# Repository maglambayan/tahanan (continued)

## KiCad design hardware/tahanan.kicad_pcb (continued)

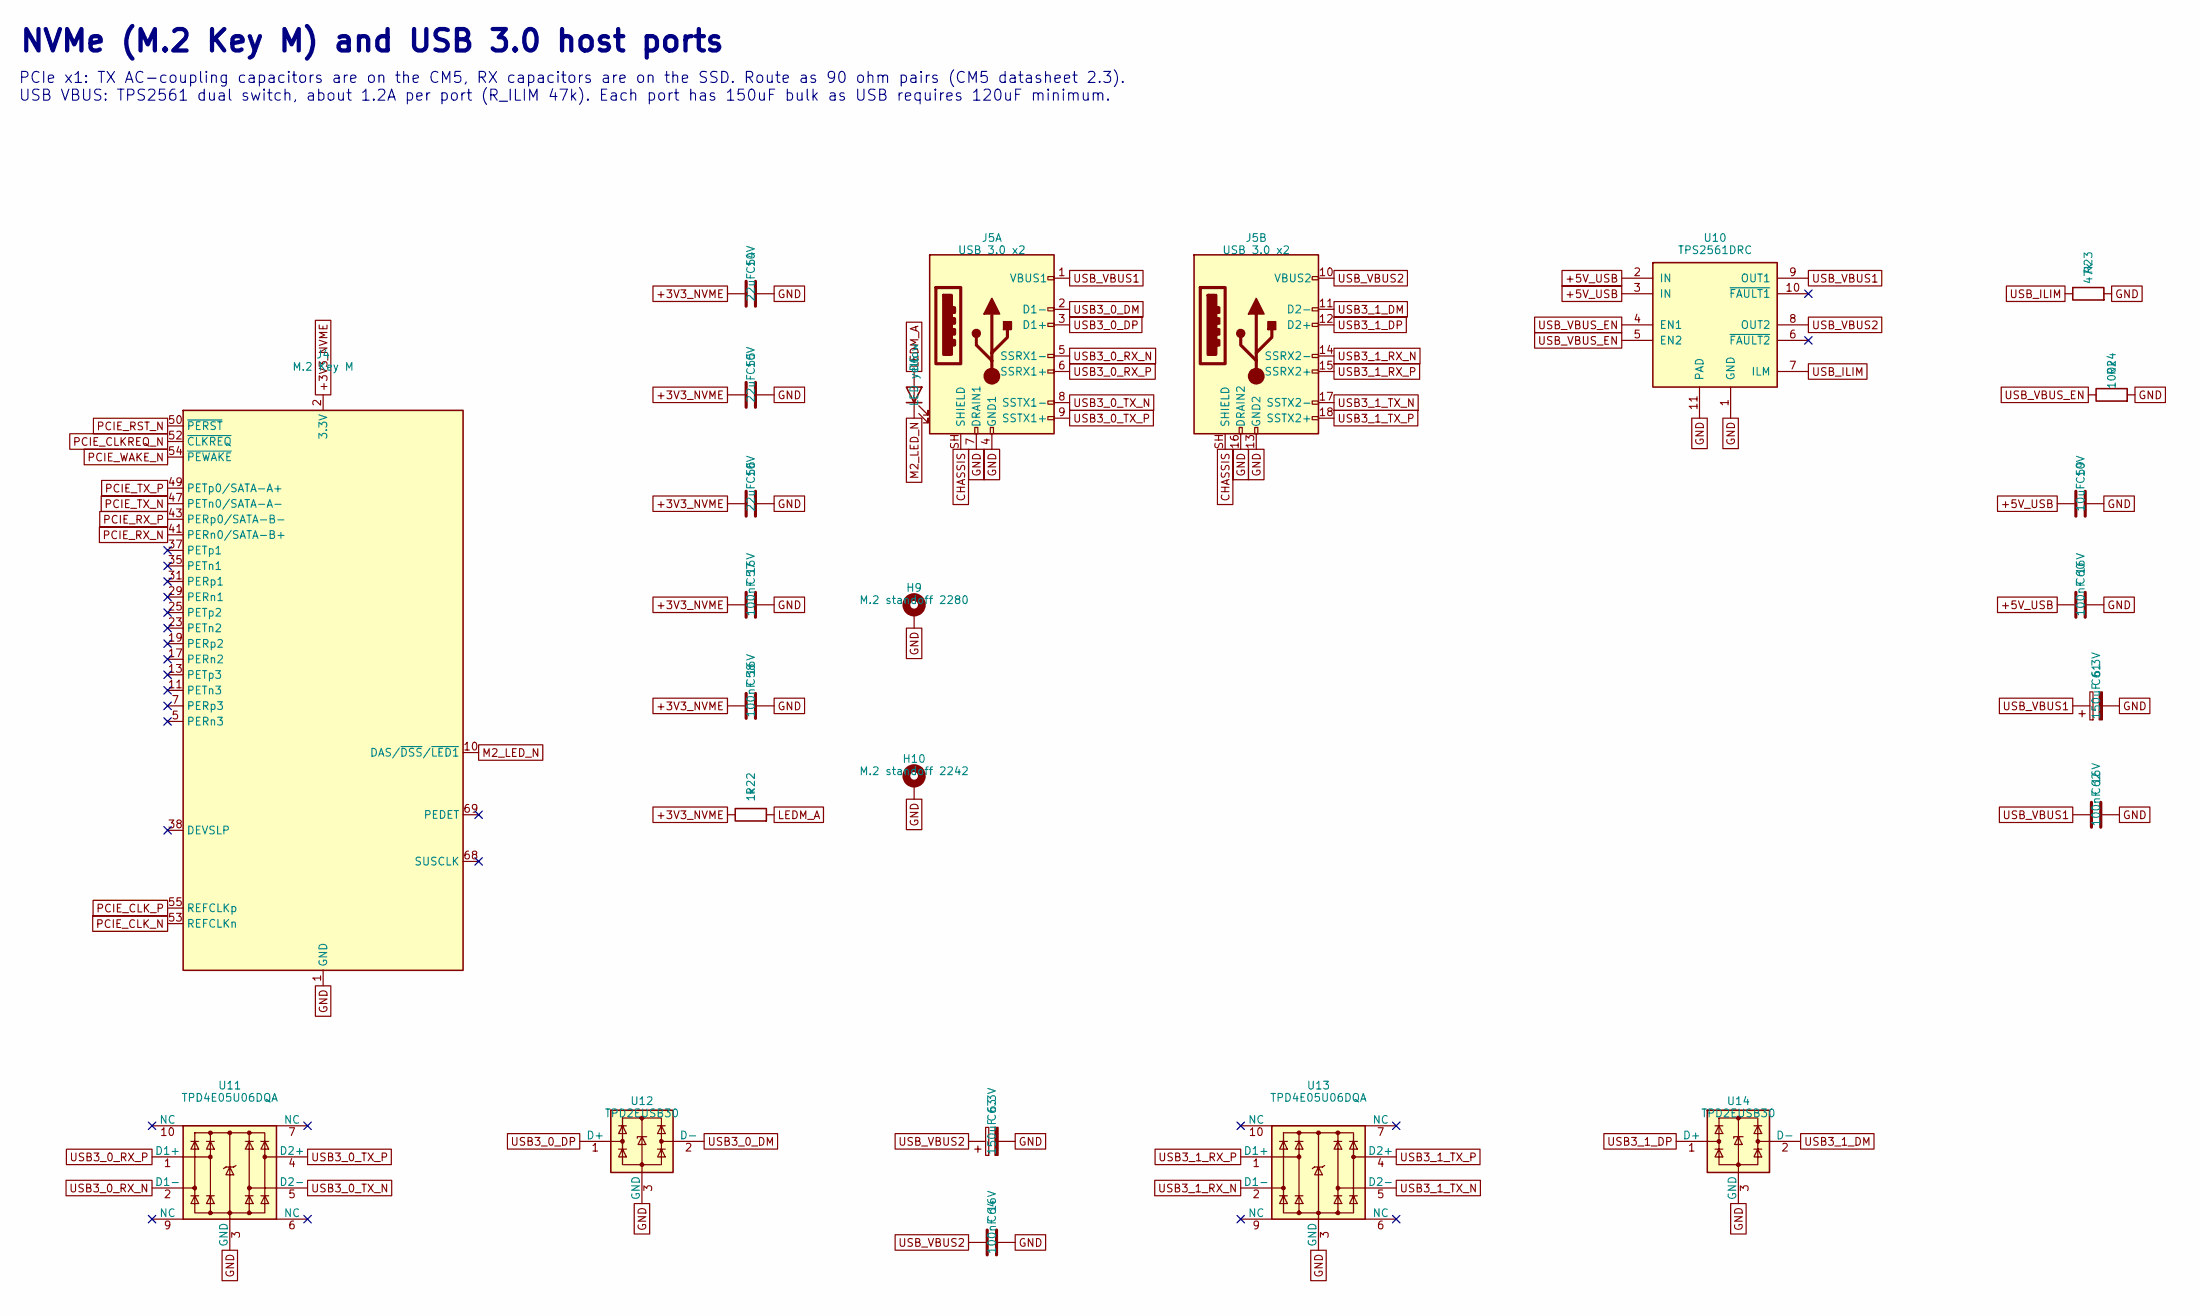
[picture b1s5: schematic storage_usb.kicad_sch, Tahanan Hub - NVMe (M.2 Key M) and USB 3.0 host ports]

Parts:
C54, C55, C56: 22uF 10V; C_0805_2012Metric; MPN CL21A226MPQNNNE
C57, C58, C60, C62, C64: 100nF 16V; C_0402_1005Metric; MPN CL05B104KO5NNNC
C59: 10uF 10V; C_0603_1608Metric; MPN CL10A106KP8NNNC
C61, C63: 150uF 6.3V; CP_EIA-3528-21_Kemet-B; MPN T520B157M006ATE070
D6: LED yellow; LED_0603_1608Metric; MPN 150060YS75000
H9: M.2 standoff 2280; Mounting_Wuerth_WA-SMSI-M2_H2.5mm_9774025243; MPN 9774025243R
H10: M.2 standoff 2242; Mounting_Wuerth_WA-SMSI-M2_H2.5mm_9774025243; MPN 9774025243R
J4: M.2 Key M; TE_M.2_M_2x38-1MP_P0.5mm; MPN 2199119-4
J5: USB 3.0 x2; USB3_A_Molex_48406-0001_Horizontal_Stacked; MPN 48406-0001
R22: 1k; R_0402_1005Metric; MPN RC0402FR-071kL
R23: 47k; R_0402_1005Metric; MPN RC0402FR-0747kL
R24: 100k; R_0402_1005Metric; MPN RC0402FR-07100kL
U10: TPS2561DRC; VSON-10-1EP_3x3mm_P0.5mm_EP1.65x2.4mm_ThermalVias; MPN TPS2561DRCR
U11, U13: TPD4E05U06DQA; USON-10_2.5x1.0mm_P0.5mm; MPN TPD4E05U06DQAR
U12, U14: TPD2EUSB30; Texas_DRT-3; MPN TPD2EUSB30DRTR

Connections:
+3V3_NVME: C54.1, C55.1, C56.1, C57.1, C58.1, J4.2 (3.3V), J4.4 (3.3V), J4.12 (3.3V), J4.14 (3.3V), J4.16 (3.3V), J4.18 (3.3V), J4.70 (3.3V), J4.72 (3.3V), J4.74 (3.3V), R22.1; also elsewhere on the board
+5V_USB: C59.1, C60.1, U10.2 (IN), U10.3 (IN); also elsewhere on the board
CHASSIS: J5.SH (SHIELD); also elsewhere on the board
GND: C54.2, C55.2, C56.2, C57.2, C58.2, C59.2, C60.2, C61.2, C62.2, C63.2, C64.2, H9.1, H10.1, J4.1 (GND), J4.3 (GND), J4.9 (GND), J4.15 (GND), J4.21 (GND), J4.27 (GND), J4.33 (GND), J4.39 (GND), J4.45 (GND), J4.51 (GND), J4.57 (GND), J4.71 (GND), J4.73 (GND), J4.75 (GND), J5.4 (GND1), J5.7 (DRAIN1), J5.13 (GND2), J5.16 (DRAIN2), R23.2, R24.2, U10.1 (GND), U10.11 (PAD), U11.3 (GND), U11.8 (GND), U12.3 (GND), U13.3 (GND), U13.8 (GND), U14.3 (GND); also elsewhere on the board
LEDM_A: D6.2 (A), R22.2
M2_LED_N: D6.1 (K), J4.10 (DAS/~DSS/~LED1)
PCIE_CLKREQ_N: J4.52 (~CLKREQ); also elsewhere on the board
PCIE_CLK_N: J4.53 (REFCLKn); also elsewhere on the board
PCIE_CLK_P: J4.55 (REFCLKp); also elsewhere on the board
PCIE_RST_N: J4.50 (~PERST); also elsewhere on the board
PCIE_RX_N: J4.41 (PERn0/SATA-B+); also elsewhere on the board
PCIE_RX_P: J4.43 (PERp0/SATA-B-); also elsewhere on the board
PCIE_TX_N: J4.47 (PETn0/SATA-A-); also elsewhere on the board
PCIE_TX_P: J4.49 (PETp0/SATA-A+); also elsewhere on the board
PCIE_WAKE_N: J4.54 (~PEWAKE); also elsewhere on the board
USB3_0_DM: J5.2 (D1-), U12.2 (D-); also elsewhere on the board
USB3_0_DP: J5.3 (D1+), U12.1 (D+); also elsewhere on the board
USB3_0_RX_N: J5.5 (SSRX1-), U11.2 (D1-); also elsewhere on the board
USB3_0_RX_P: J5.6 (SSRX1+), U11.1 (D1+); also elsewhere on the board
USB3_0_TX_N: J5.8 (SSTX1-), U11.5 (D2-); also elsewhere on the board
USB3_0_TX_P: J5.9 (SSTX1+), U11.4 (D2+); also elsewhere on the board
USB3_1_DM: J5.11 (D2-), U14.2 (D-); also elsewhere on the board
USB3_1_DP: J5.12 (D2+), U14.1 (D+); also elsewhere on the board
USB3_1_RX_N: J5.14 (SSRX2-), U13.2 (D1-); also elsewhere on the board
USB3_1_RX_P: J5.15 (SSRX2+), U13.1 (D1+); also elsewhere on the board
USB3_1_TX_N: J5.17 (SSTX2-), U13.5 (D2-); also elsewhere on the board
USB3_1_TX_P: J5.18 (SSTX2+), U13.4 (D2+); also elsewhere on the board
USB_ILIM: R23.1, U10.7 (ILM)
USB_VBUS1: C61.1, C62.1, J5.1 (VBUS1), U10.9 (OUT1)
USB_VBUS2: C63.1, C64.1, J5.10 (VBUS2), U10.8 (OUT2)
USB_VBUS_EN: R24.1, U10.4 (EN1), U10.5 (EN2); also elsewhere on the board

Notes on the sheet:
NVMe (M.2 Key M) and USB 3.0 host ports
PCIe x1: TX AC-coupling capacitors are on the CM5, RX capacitors are on the SSD. Route as 90 ohm pairs (CM5 datasheet 2.3). USB VBUS: TPS2561 dual switch, about 1.2A per port (R_ILIM 47k). Each port has 150uF bulk as USB requires 120uF minimum.

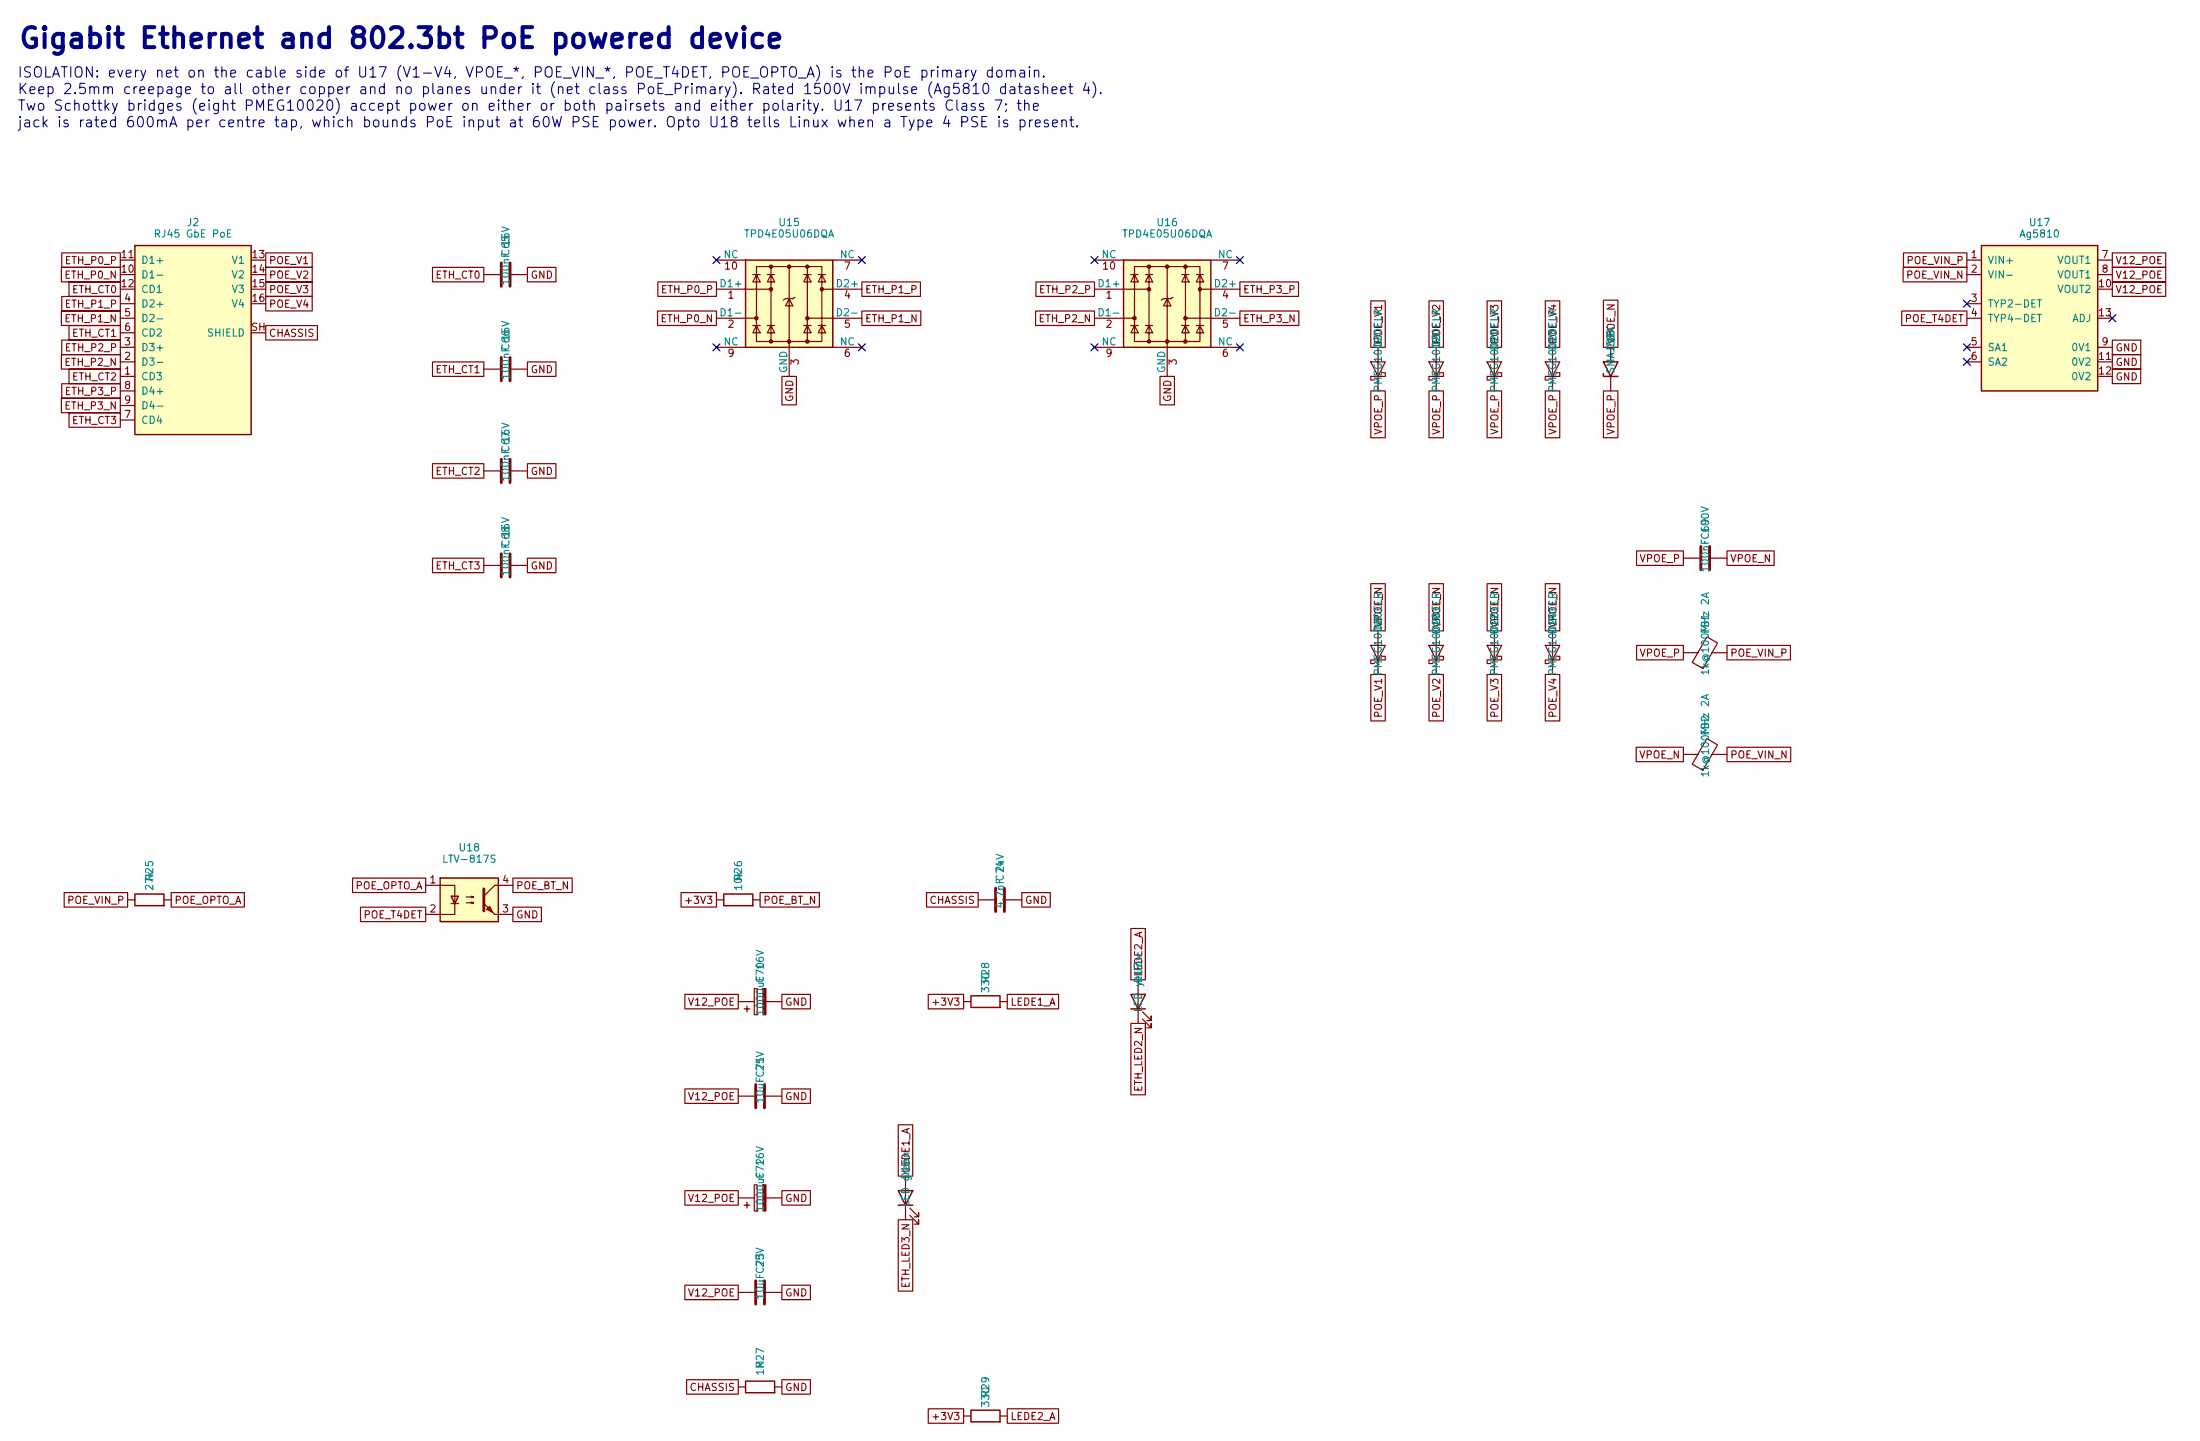
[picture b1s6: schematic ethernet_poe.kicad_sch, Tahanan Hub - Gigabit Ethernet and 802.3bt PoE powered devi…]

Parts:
C65, C66, C67, C68: 100nF 16V; C_0402_1005Metric; MPN CL05B104KO5NNNC
C69: 100nF 100V; C_0805_2012Metric; MPN CL21B104KCFNNNE
C70, C72: 1000uF 16V; CP_Elec_10x10.5; MPN EEE-FT1C102AP
C71, C73: 10uF 25V; C_1206_3216Metric; MPN CL31B106KAHNNNE
C74: 4.7nF 2kV; C_1812_4532Metric; MPN C1812C472KGRACTU
D7, D8, D9, D10, D11, D12, D13, D14: PMEG10020ELR; Nexperia_CFP3_SOD-123W; MPN PMEG10020ELRX
D15: SMAJ58A; D_SMA; MPN SMAJ58A
D16: LED green; LED_0603_1608Metric; MPN 150060GS75000
D17: LED yellow; LED_0603_1608Metric; MPN 150060YS75000
FB1, FB2: 1k@100MHz 2A; L_1210_3225Metric; MPN FBMH3225HM102NT
J2: RJ45 GbE PoE; RJ45_Wuerth_7499511001A; MPN 7499511001A
R25: 27k; R_1206_3216Metric; MPN RC1206FR-0727kL
R26: 10k; R_0402_1005Metric; MPN RC0402FR-0710kL
R27: 1M; R_1206_3216Metric; MPN RC1206FR-071ML
R28, R29: 330; R_0402_1005Metric; MPN RC0402FR-07330RL
U15, U16: TPD4E05U06DQA; USON-10_2.5x1.0mm_P0.5mm; MPN TPD4E05U06DQAR
U17: Ag5810; Silvertel_Ag5810; MPN Ag5810
U18: LTV-817S; SMDIP-4_W9.53mm; MPN LTV-817S

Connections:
+3V3: R26.1, R28.1, R29.1; also elsewhere on the board
CHASSIS: C74.1, J2.SH (SHIELD), R27.1; also elsewhere on the board
ETH_CT0: C65.1, J2.12 (CD1)
ETH_CT1: C66.1, J2.6 (CD2)
ETH_CT2: C67.1, J2.1 (CD3)
ETH_CT3: C68.1, J2.7 (CD4)
ETH_LED2_N: D17.1 (K); also elsewhere on the board
ETH_LED3_N: D16.1 (K); also elsewhere on the board
ETH_P0_N: J2.10 (D1-), U15.2 (D1-); also elsewhere on the board
ETH_P0_P: J2.11 (D1+), U15.1 (D1+); also elsewhere on the board
ETH_P1_N: J2.5 (D2-), U15.5 (D2-); also elsewhere on the board
ETH_P1_P: J2.4 (D2+), U15.4 (D2+); also elsewhere on the board
ETH_P2_N: J2.2 (D3-), U16.2 (D1-); also elsewhere on the board
ETH_P2_P: J2.3 (D3+), U16.1 (D1+); also elsewhere on the board
ETH_P3_N: J2.9 (D4-), U16.5 (D2-); also elsewhere on the board
ETH_P3_P: J2.8 (D4+), U16.4 (D2+); also elsewhere on the board
GND: C65.2, C66.2, C67.2, C68.2, C70.2, C71.2, C72.2, C73.2, C74.2, R27.2, U15.3 (GND), U15.8 (GND), U16.3 (GND), U16.8 (GND), U17.9 (0V1), U17.11 (0V2), U17.12 (0V2), U18.3; also elsewhere on the board
LEDE1_A: D16.2 (A), R28.2
LEDE2_A: D17.2 (A), R29.2
POE_BT_N: R26.2, U18.4; also elsewhere on the board
POE_OPTO_A: R25.2, U18.1
POE_T4DET: U17.4 (TYP4-DET), U18.2
POE_V1: D7.2 (A), D8.1 (K), J2.13 (V1)
POE_V2: D9.2 (A), D10.1 (K), J2.14 (V2)
POE_V3: D11.2 (A), D12.1 (K), J2.15 (V3)
POE_V4: D13.2 (A), D14.1 (K), J2.16 (V4)
POE_VIN_N: FB2.2, U17.2 (VIN-)
POE_VIN_P: FB1.2, R25.1, U17.1 (VIN+)
V12_POE: C70.1, C71.1, C72.1, C73.1, U17.7 (VOUT1), U17.8 (VOUT1), U17.10 (VOUT2); also elsewhere on the board
VPOE_N: C69.2, D8.2 (A), D10.2 (A), D12.2 (A), D14.2 (A), D15.2 (A2), FB2.1
VPOE_P: C69.1, D7.1 (K), D9.1 (K), D11.1 (K), D13.1 (K), D15.1 (A1), FB1.1

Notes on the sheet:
Gigabit Ethernet and 802.3bt PoE powered device
ISOLATION: every net on the cable side of U17 (V1-V4, VPOE_*, POE_VIN_*, POE_T4DET, POE_OPTO_A) is the PoE primary domain. Keep 2.5mm creepage to all other copper and no planes under it (net class PoE_Primary). Rated 1500V impulse (Ag5810 datasheet 4). Two Schottky bridges (eight PMEG10020) accept 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

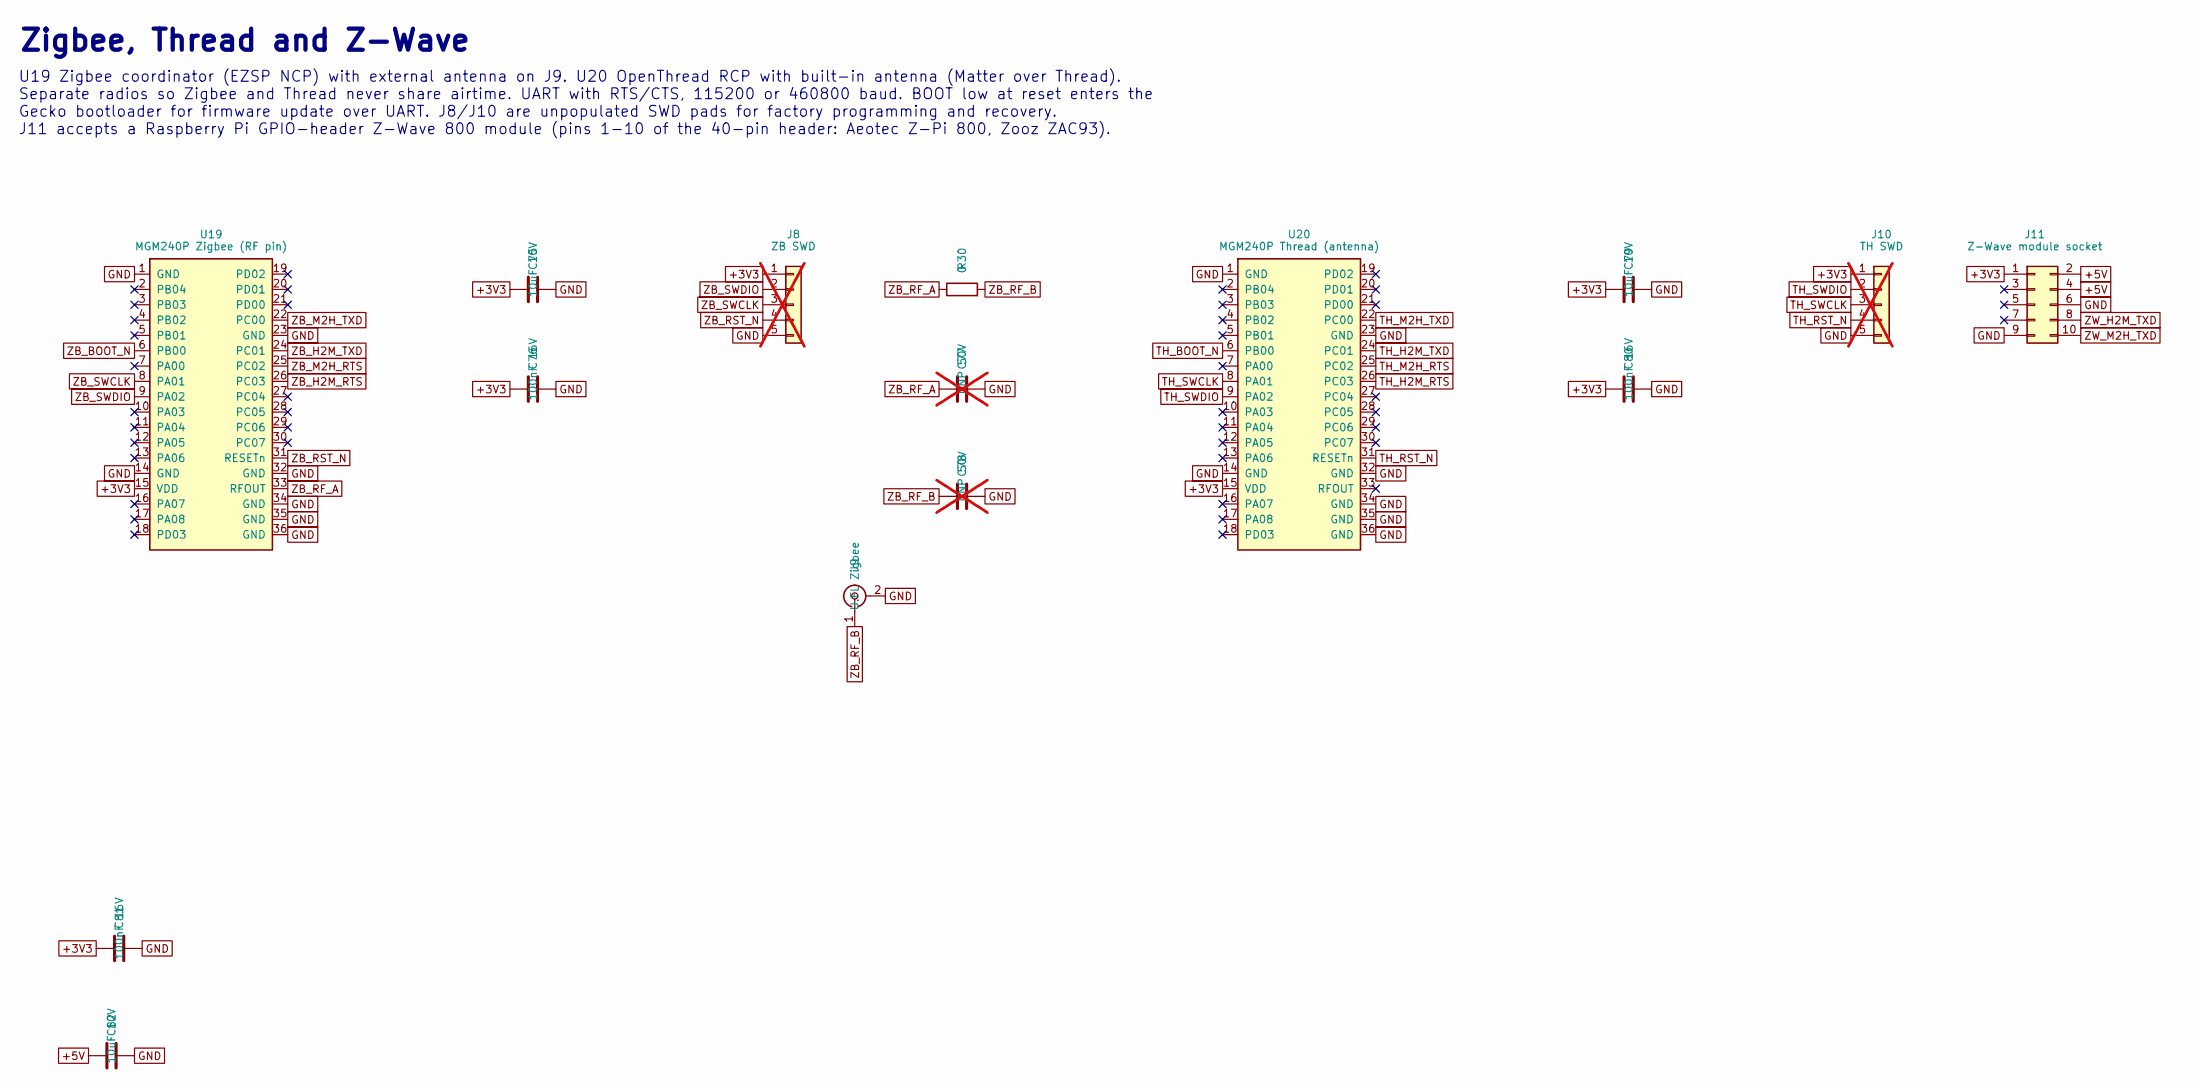
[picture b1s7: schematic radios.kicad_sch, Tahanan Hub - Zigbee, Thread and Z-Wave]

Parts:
C75, C79, C82: 10uF 10V; C_0603_1608Metric; MPN CL10A106KP8NNNC
C76, C80, C81: 100nF 16V; C_0402_1005Metric; MPN CL05B104KO5NNNC
C77, C78: DNP 50V; C_0402_1005Metric; not fitted
J8: ZB SWD; PinHeader_1x05_P1.27mm_Vertical; not fitted
J9: U.FL Zigbee; U.FL_Hirose_U.FL-R-SMT-1_Vertical; MPN U.FL-R-SMT-1(80)
J10: TH SWD; PinHeader_1x05_P1.27mm_Vertical; not fitted
J11: Z-Wave module socket; PinSocket_2x05_P2.54mm_Vertical; MPN SSW-105-01-G-D
R30: 0; R_0402_1005Metric; MPN RC0402FR-070RL
U19: MGM240P Zigbee (RF pin); SiliconLabs_MGM240P; MPN MGM240PA32VNN3
U20: MGM240P Thread (antenna); SiliconLabs_MGM240P; MPN MGM240PA32VNA3

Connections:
+3V3: C75.1, C76.1, C79.1, C80.1, C81.1, J8.1, J10.1, J11.1, U19.15 (VDD), U20.15 (VDD); also elsewhere on the board
+5V: C82.1, J11.2, J11.4; also elsewhere on the board
GND: C75.2, C76.2, C77.2, C78.2, C79.2, C80.2, C81.2, C82.2, J8.5, J9.2 (Ext), J10.5, J11.6, J11.9, U19.1 (GND), U19.14 (GND), U19.23 (GND), U19.32 (GND), U19.34 (GND), U19.35 (GND), U19.36 (GND), U20.1 (GND), U20.14 (GND), U20.23 (GND), U20.32 (GND), U20.34 (GND), U20.35 (GND), U20.36 (GND); also elsewhere on the board
TH_BOOT_N: U20.6 (PB00); also elsewhere on the board
TH_H2M_RTS: U20.26 (PC03); also elsewhere on the board
TH_H2M_TXD: U20.24 (PC01); also elsewhere on the board
TH_M2H_RTS: U20.25 (PC02); also elsewhere on the board
TH_M2H_TXD: U20.22 (PC00); also elsewhere on the board
TH_RST_N: J10.4, U20.31 (RESETn); also elsewhere on the board
TH_SWCLK: J10.3, U20.8 (PA01)
TH_SWDIO: J10.2, U20.9 (PA02)
ZB_BOOT_N: U19.6 (PB00); also elsewhere on the board
ZB_H2M_RTS: U19.26 (PC03); also elsewhere on the board
ZB_H2M_TXD: U19.24 (PC01); also elsewhere on the board
ZB_M2H_RTS: U19.25 (PC02); also elsewhere on the board
ZB_M2H_TXD: U19.22 (PC00); also elsewhere on the board
ZB_RF_A: C77.1, R30.1, U19.33 (RFOUT)
ZB_RF_B: C78.1, J9.1 (In), R30.2
ZB_RST_N: J8.4, U19.31 (RESETn); also elsewhere on the board
ZB_SWCLK: J8.3, U19.8 (PA01)
ZB_SWDIO: J8.2, U19.9 (PA02)
ZW_H2M_TXD: J11.8; also elsewhere on the board
ZW_M2H_TXD: J11.10; also elsewhere on the board

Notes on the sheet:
Zigbee, Thread and Z-Wave
U19 Zigbee coordinator (EZSP NCP) with external antenna on J9. U20 OpenThread RCP with built-in antenna (Matter over Thread). Separate radios so Zigbee and Thread never share airtime. UART with RTS/CTS, 115200 or 460800 baud. BOOT low at reset enters the Gecko bootloader for firmware update over UA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

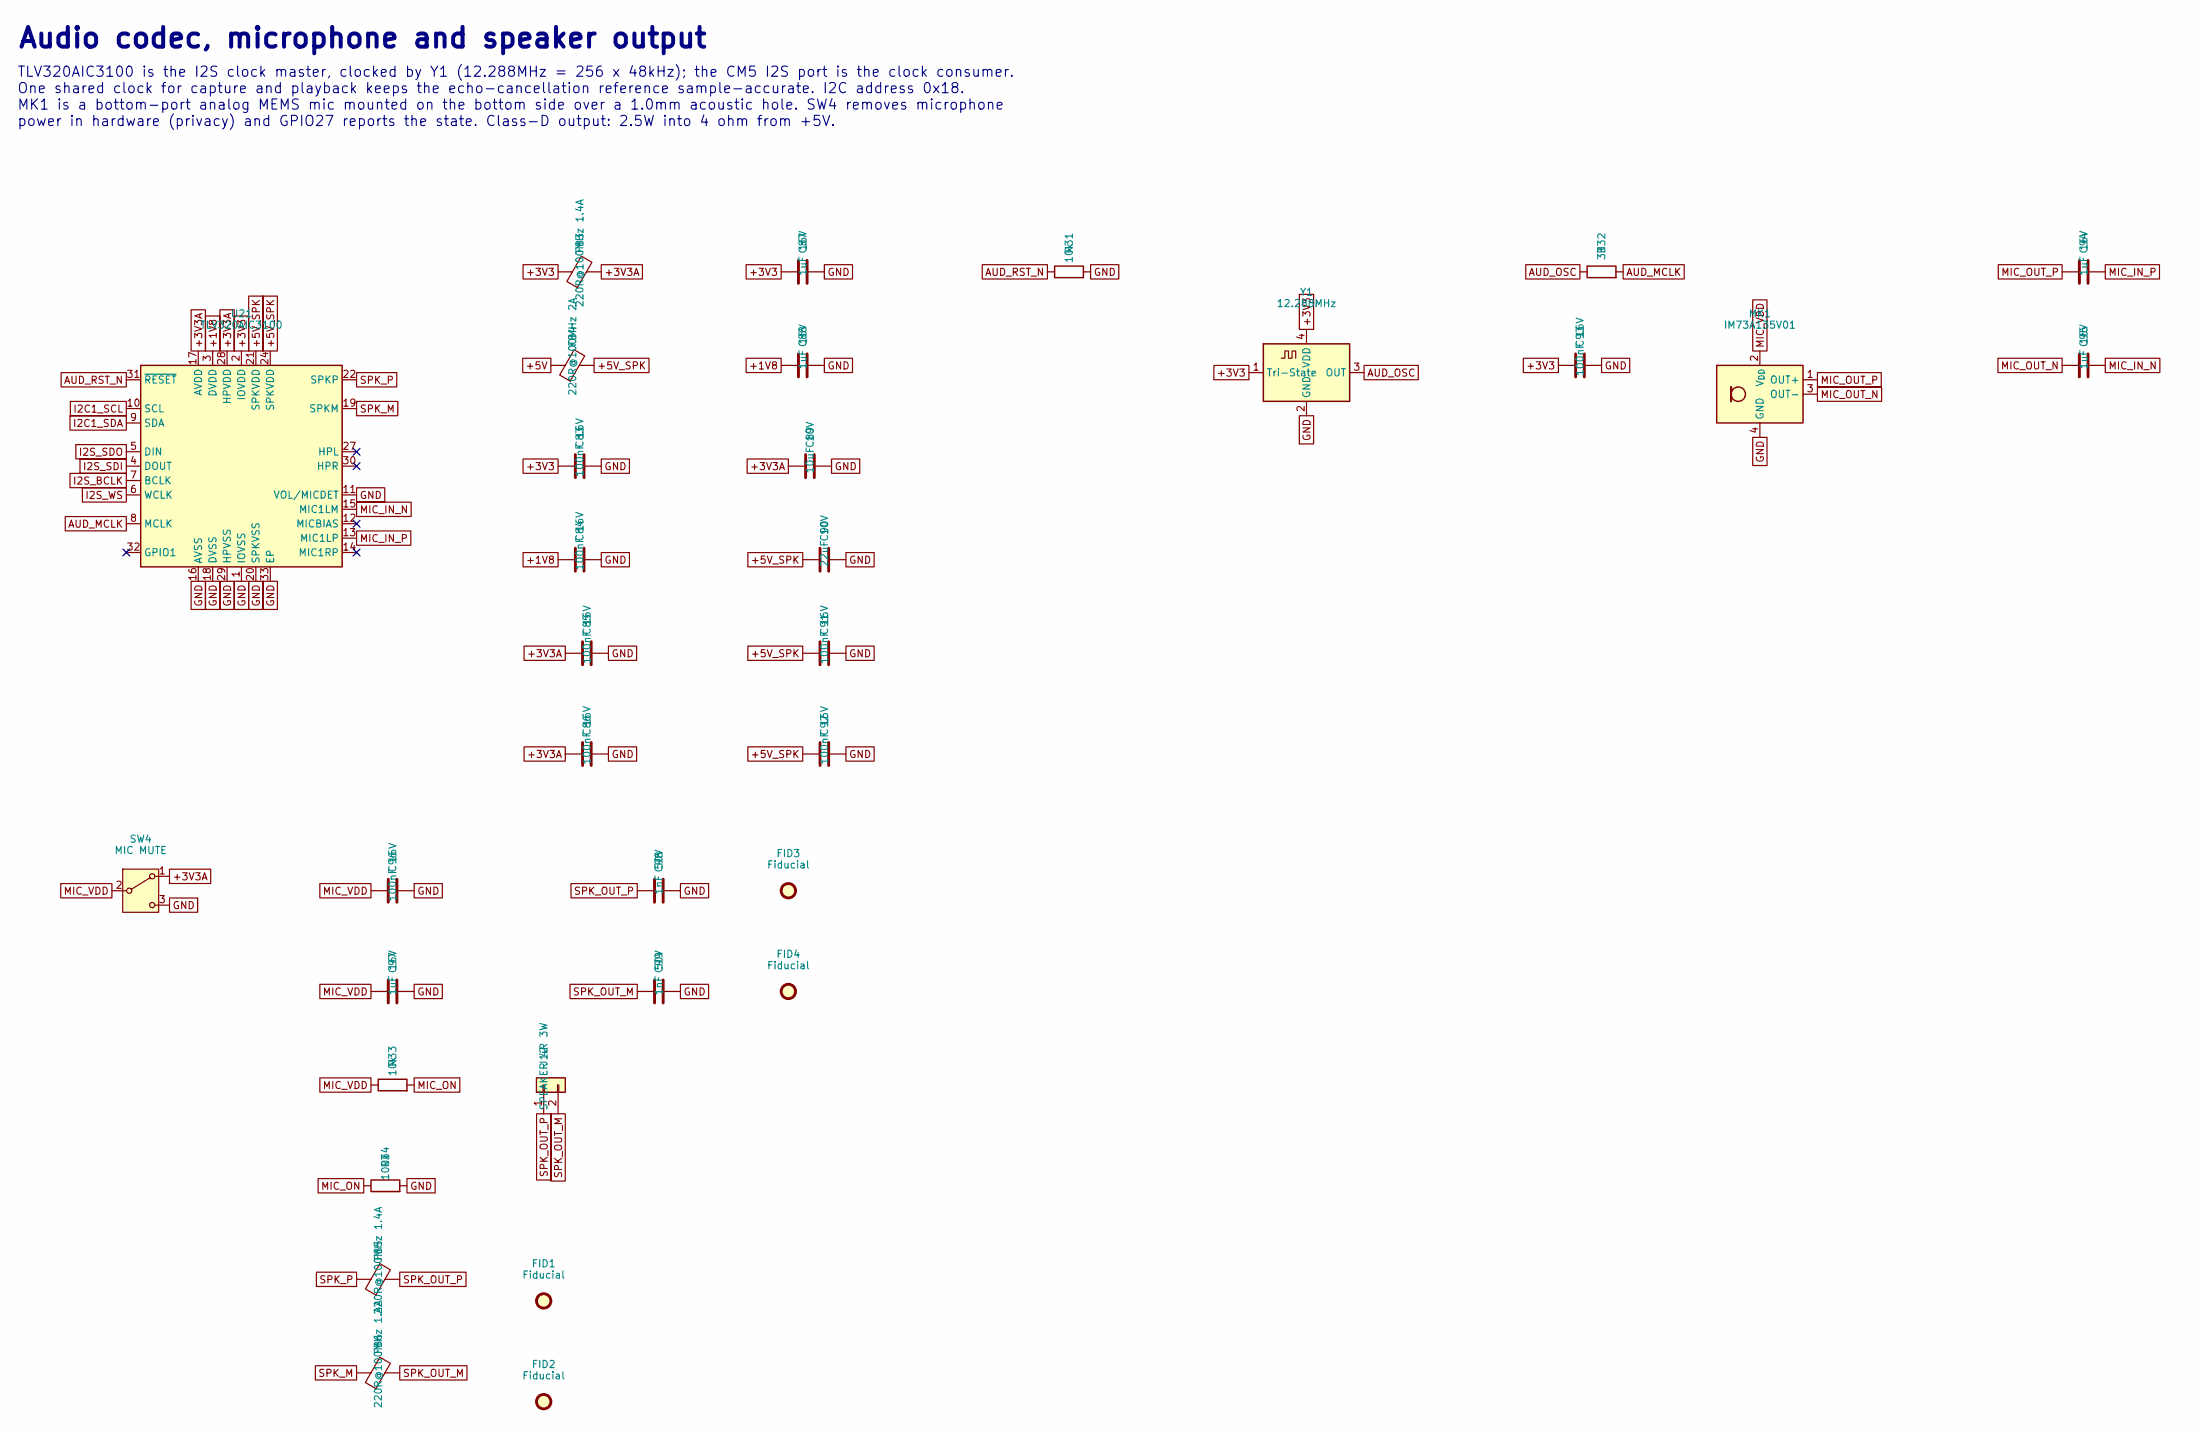
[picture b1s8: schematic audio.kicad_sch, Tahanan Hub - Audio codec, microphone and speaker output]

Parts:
C83, C84, C85, C86, C91, C92, C93, C96: 100nF 16V; C_0402_1005Metric; MPN CL05B104KO5NNNC
C87, C88, C94, C95, C97: 1uF 16V; C_0402_1005Metric; MPN CL05A105KO5NNNC
C89: 10uF 10V; C_0603_1608Metric; MPN CL10A106KP8NNNC
C90: 22uF 10V; C_0805_2012Metric; MPN CL21A226MPQNNNE
C98, C99: 1nF 50V; C_0402_1005Metric; MPN CL05B102KB5NNNC
FB3, FB5, FB6: 220R@100MHz 1.4A; L_0603_1608Metric; MPN BLM18PG221SN1D
FB4: 220R@100MHz 2A; L_0805_2012Metric; MPN BLM21PG221SN1D
FID1, FID2, FID3, FID4: Fiducial; Fiducial_1mm_Mask2mm
J12: SPEAKER 4R 3W; JST_PH_S2B-PH-K_1x02_P2.00mm_Horizontal; MPN S2B-PH-K-S
MK1: IM73A135V01; Infineon_PG-LLGA-5-2; MPN IM73A135V01XTSA1
R31, R33: 10k; R_0402_1005Metric; MPN RC0402FR-0710kL
R32: 33; R_0402_1005Metric; MPN RC0402FR-0733RL
R34: 100k; R_0402_1005Metric; MPN RC0402FR-07100kL
SW4: MIC MUTE; SW_SPDT_CK_JS102011SAQN; MPN JS102011SAQN
U21: TLV320AIC3100; VQFN-32-1EP_5x5mm_P0.5mm_EP3.5x3.5mm; MPN TLV320AIC3100IRHBR
Y1: 12.288MHz; Oscillator_SMD_ECS_2520MV-xxx-xx-4Pin_2.5x2.0mm; MPN ECS-2520MVLC-122.8-BN-TR

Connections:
+1V8: C84.1, C88.1, U21.3 (DVDD); also elsewhere on the board
+3V3: C83.1, C87.1, C93.1, FB3.1, U21.2 (IOVDD), Y1.1 (Tri-State), Y1.4 (VDD); also elsewhere on the board
+3V3A: C85.1, C86.1, C89.1, FB3.2, SW4.1 (A), U21.17 (AVDD), U21.28 (HPVDD)
+5V: FB4.1; also elsewhere on the board
+5V_SPK: C90.1, C91.1, C92.1, FB4.2, U21.21 (SPKVDD), U21.24 (SPKVDD)
AUD_MCLK: R32.2, U21.8 (MCLK)
AUD_OSC: R32.1, Y1.3 (OUT)
AUD_RST_N: R31.1, U21.31 (~RESET); also elsewhere on the board
GND: C83.2, C84.2, C85.2, C86.2, C87.2, C88.2, C89.2, C90.2, C91.2, C92.2, C93.2, C96.2, C97.2, C98.2, C99.2, MK1.4 (GND), MK1.5 (GND), R31.2, R34.2, SW4.3 (C), U21.1 (IOVSS), U21.11 (VOL/MICDET), U21.16 (AVSS), U21.18 (DVSS), U21.20 (SPKVSS), U21.25 (SPKVSS), U21.29 (HPVSS), U21.33 (EP), Y1.2 (GND); also elsewhere on the board
I2C1_SCL: U21.10 (SCL); also elsewhere on the board
I2C1_SDA: U21.9 (SDA); also elsewhere on the board
I2S_BCLK: U21.7 (BCLK); also elsewhere on the board
I2S_SDI: U21.4 (DOUT); also elsewhere on the board
I2S_SDO: U21.5 (DIN); also elsewhere on the board
I2S_WS: U21.6 (WCLK); also elsewhere on the board
MIC_IN_N: C95.2, U21.15 (MIC1LM)
MIC_IN_P: C94.2, U21.13 (MIC1LP)
MIC_ON: R33.2, R34.1; also elsewhere on the board
MIC_OUT_N: C95.1, MK1.3 (OUT-)
MIC_OUT_P: C94.1, MK1.1 (OUT+)
MIC_VDD: C96.1, C97.1, MK1.2 (V_{DD}), R33.1, SW4.2 (B)
SPK_M: FB6.1, U21.19 (SPKM), U21.23 (SPKM)
SPK_OUT_M: C99.1, FB6.2, J12.2
SPK_OUT_P: C98.1, FB5.2, J12.1
SPK_P: FB5.1, U21.22 (SPKP), U21.26 (SPKP)

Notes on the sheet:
Audio codec, microphone and speaker output
TLV320AIC3100 is the I2S clock master, clocked by Y1 (12.288MHz = 256 x 48kHz); the CM5 I2S port is the clock consumer. One shared clock for capture and playback keeps the echo-cancellation reference sample-accurate. I2C address 0x18. MK1 is a bottom-port analog MEMS mic mounted on the bottom side 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

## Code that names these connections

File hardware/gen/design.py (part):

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     'USB Type-C receptacle, USB 2.0, 16 pin, top mount', alt='HRO TYPE-C-31-M-12 (different footprint)', ref='J1')
part('U', 'STUSB4500QTR',
     {'CC1': 'USBC_CC1', 'CC1DB': 'USBC_CC1', 'CC2': 'USBC_CC2', 'CC2DB': 'USBC_CC2', 'NC': 'NC', 'RESET': G, 'SCL': 'I2C1_SCL', 'SDA': 'I2C1_SDA',
      'DISCH': 'PD_DISCH', 'GND': G, 'ATTACH': 'NC', 'ADDR0': G, 'ADDR1': G, 'POWER_OK3': 'NC', 'GPIO': 'NC', 'VBUS_EN_SNK': 'PD_VBUS_EN_N',
      'A_B_SIDE': 'NC', 'VBUS_VS_DISCH': 'PD_VS_DISCH', 'ALERT': 'NC', 'POWER_OK2': 'NC', 'VREG_1V2': 'PD_1V2', 'VSYS': G, 'VREG_2V7': 'PD_2V7', 'VDD': 'VBUS'},
     mpn='STUSB4500QTR', mfr='STMicroelectronics', alt='STUSB4500LQTR (5V-only variant is NOT a substitute)', ref='U1')
c1u('PD_1V2'); c1u('PD_2V7'); C('4.7uF', 'VBUS', G, '0805', '50V', mpn='CL21A475KBQNNNE', mfr='Samsung', diel='X5R')
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# =====================================================================================
sheet('power_rails', 'Regulators and sequencing',
      'Sequence: VIN>8V -> +5V (U5) -> PG_5V enables +5V_USB (U6). CM5 starts from +5V; CM5_3V3 then enables +3V3 (U8).\n'
      '+3V3_NVME (U7) is enabled by PCIE_PWR_EN from the CM5. Nothing drives a CM5 pin before +5V is valid (CM5 datasheet 3.1).\n'
      'LMR336x0: VFB=1.0V. 5V: 100k/24.9k. 3.3V: 100k/43.2k. fsw=400kHz, L=6.8uH, CIN 2x10uF+220nF (datasheet table 9-1).')
def lmr(sym, tag, out, en, L, lmpn, rb):
    part('U', sym, {'GND': G, 'VIN': 'VIN', 'EN': en, 'PG': f'PG_{tag}', 'FB': f'FB_{tag}', 'VCC': f'VCC_{tag}', 'BOOT': f'BOOT_{tag}', 'SW': f'SW_{tag}'},
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      'CC1/CC2 are not used: PD is handled by U1, so set PSU_MAX_CURRENT=5000 in the bootloader EEPROM config.\n'
      'GPIO map: 2/3 I2C1, 4-7 UART2 Zigbee, 8-11 UART3 Thread, 12/13 UART4 console, 14/15 UART0 Z-Wave socket,\n'
      '16 codec reset, 17 user button, 18-21 I2S, 22/23 Zigbee RST/BOOT, 24/25 Thread RST/BOOT, 26 user LED, 27 mic-enabled sense.')
A = {'GND': G, '5V': '+5V', 'CM5_3.3V': 'CM5_3V3', 'GPIO_VREF': 'CM5_3V3', 'CM5_1.8V': 'NC', 'VBAT': 'VBAT'}
for i in range(4):
    A[f'Ethernet_Pair{i}_P'] = f'ETH_P{i}_P'; A[f'Ethernet_Pair{i}_N'] = f'ETH_P{i}_N'
A.update({'Ethernet_nLED3': 'ETH_LED3_N', 'Ethernet_nLED2': 'ETH_LED2_N', 'Ethernet_SYNC_OUT': 'NC', 'Fan_Tacho': 'FAN_TACH', 'Fan_PWM': 'FAN_PWM',
          'EEPROM_nWP': 'EEPROM_NWP', 'LED_nACT': 'LED_ACT_N', 'LED_nPWR': 'LED_PWR_N', 'ID_SC': 'NC', 'ID_SD': 'NC', 'SCL0': 'NC', 'SDA0': 'NC',
          'WL_nDisable': 'NC', 'BT_nDisable': 'NC', 'PWR_Button': 'PWR_BTN_N', 'nRPIBOOT': 'RPIBOOT_N', 'CC1': 'NC', 'CC2': 'NC',
          'CAM_GPIO0': 'POE_BT_N', 'CAM_GPIO1': 'NC', 'PMIC_Enable': 'NC', 'SD_VDD_OVERRIDE': 'NC', 'SD_PWR_ON': 'NC',
          'GPIO2': 'I2C1_SDA', 'GPIO3': 'I2C1_SCL', 'GPIO4': 'ZB_H2M_TXD', 'GPIO5': 'ZB_M2H_TXD', 'GPIO6': 'ZB_M2H_RTS', 'GPIO7': 'ZB_H2M_RTS',
          'GPIO8': 'TH_H2M_TXD', 'GPIO9': 'TH_M2H_TXD', 'GPIO10': 'TH_M2H_RTS', 'GPIO11': 'TH_H2M_RTS', 'GPIO12': 'DBG_TXD', 'GPIO13': 'DBG_RXD',
          'GPIO14': 'ZW_H2M_TXD', 'GPIO15': 'ZW_M2H_TXD', 'GPIO16': 'AUD_RST_N', 'GPIO17': 'USER_BTN_N', 'GPIO18': 'I2S_BCLK', 'GPIO19': 'I2S_WS',
          'GPIO20': 'I2S_SDI', 'GPIO21': 'I2S_SDO', 'GPIO22': 'ZB_RST_N', 'GPIO23': 'ZB_BOOT_N', 'GPIO24': 'TH_RST_N', 'GPIO25': 'TH_BOOT_N',
          'GPIO26': 'USER_LED', 'GPIO27': 'MIC_ON'})
for n in ('CLK', 'CMD', 'DAT0', 'DAT1', 'DAT2', 'DAT3', 'DAT4', 'DAT5', 'DAT6', 'DAT7'): A['SD_' + n] = 'NC'
CONN = dict(fp='Connector_Hirose_DF40:Hirose_DF40HC(3.0)-100DS-0.4V_2x50_P0.4mm', mpn='DF40HC(3.0)-100DS-0.4V(51)', mfr='Hirose',
            alt='Amphenol 10164227-1004A1RLF (4.0mm stack; confirm land pattern and change standoffs to 4.0mm)')
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R('1k', '+3V3', 'LEDP_A'); led('red', 'LEDP_A', 'LED_PWR_N'); R('1k', '+3V3', 'LEDA_A'); led('green', 'LEDA_A', 'LED_ACT_N')
R('1k', 'USER_LED', 'LEDU_A'); led('blue', 'LEDU_A', G)
part('BT', 'Device:Battery_Cell', {'+': 'VBAT', '-': G}, 'CR1220', 'Battery:BatteryHolder_Keystone_3000_1x12mm', '3000', 'Keystone', 'Coin cell holder 12mm, RTC backup')
part('J', 'Conn_01x04_MountingPin', {1: '+5V', 2: 'FAN_PWM', 3: G, 4: 'FAN_TACH', 'MP': G}, 'FAN', 'Connector_JST:JST_SH_SM04B-SRSS-TB_1x04-1MP_P1.00mm_Horizontal',
     'SM04B-SRSS-TB', 'JST', '4-pin 1.0mm fan header, Raspberry Pi 5 fan pinout')
part('J', 'Connector_Generic:Conn_01x03', {1: G, 2: 'DBG_TXD', 3: 'DBG_RXD'}, 'CONSOLE 3V3', 'Connector_PinHeader_2.54mm:PinHeader_1x03_P2.54mm_Vertical',
     '61300311121', 'Wurth', '3-pin header, serial console (UART4, 3.3V)')
tp('EEPROM_NWP', 'EEPROM_nWP'); tp('CM5_3V3', 'CM5_3V3')
for i in range(4):
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for v in ('POE_V1', 'POE_V2', 'POE_V3', 'POE_V4'):
    for a, k in ((v, 'VPOE_P'), ('VPOE_N', v)):
        part('D', 'PMEG10020ELR', {'A': a, 'K': k}, mpn='PMEG10020ELRX', mfr='Nexperia', desc='Schottky 100V 2A SOD-123W, PoE input bridge', alt='SS210')
part('D', 'Diode:SMAJ58A', {1: 'VPOE_P', 2: 'VPOE_N'}, 'SMAJ58A', mpn='SMAJ58A', mfr='Littelfuse', desc='TVS 58V unidirectional 400W SMA (pin 1 cathode to VPOE_P)')
C('100nF', 'VPOE_P', 'VPOE_N', '0805', '100V', mpn='CL21B104KCFNNNE', mfr='Samsung')
PB = dict(mpn='FBMH3225HM102NT', fp='Inductor_SMD:L_1210_3225Metric', val='1k@100MHz 2A', mfr='Taiyo Yuden')
bead('VPOE_P', 'POE_VIN_P', **PB); bead('VPOE_N', 'POE_VIN_N', **PB)
part('U', 'Ag5810', {'VIN+': 'POE_VIN_P', 'VIN-': 'POE_VIN_N', 'TYP2-DET': 'NC', 'TYP4-DET': 'POE_T4DET', 'SA1': 'NC', 'SA2': 'NC', 'VOUT1': 'V12_POE', 'VOUT2': 'V12_POE',
                    '0V1': G, '0V2': G, 'ADJ': 'NC'}, mpn='Ag5810', mfr='Silvertel', alt='Ag5800 (85W, larger footprint)')
R('27k', 'POE_VIN_P', 'POE_OPTO_A', '1206', desc='Resistor 27k 1% 1206 0.25W, opto LED current limit from 57V')
part('U', 'LTV-817S', {1: 'POE_OPTO_A', 2: 'POE_T4DET', 3: G, 4: 'POE_BT_N'}, mpn='LTV-817S', mfr='Lite-On', desc='Optocoupler 5kV, PoE Type 4 detect across the isolation barrier', alt='PC817X (SMD), TLP785')
R('10k', '+3V3', 'POE_BT_N')
for _ in range(2):
    part('C', 'Device:C_Polarized', {1: 'V12_POE', 2: G}, '1000uF 16V', 'Capacitor_SMD:CP_Elec_10x10.5', 'EEE-FT1C102AP', 'Panasonic', 'Aluminium electrolytic 1000uF 16V, required by Ag5810')
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      'Gecko bootloader for firmware update over UART. J8/J10 are unpopulated SWD pads for factory programming and recovery.\n'
      'J11 accepts a Raspberry Pi GPIO-header Z-Wave 800 module (pins 1-10 of the 40-pin header: Aeotec Z-Pi 800, Zooz ZAC93).')
def mgm(tag, mpn, rf, val):
    n = {'GND': G, 'VDD': '+3V3', 'PC00': f'{tag}_M2H_TXD', 'PC01': f'{tag}_H2M_TXD', 'PC02': f'{tag}_M2H_RTS', 'PC03': f'{tag}_H2M_RTS', 'PB00': f'{tag}_BOOT_N',
         'RESETn': f'{tag}_RST_N', 'PA01': f'{tag}_SWCLK', 'PA02': f'{tag}_SWDIO', 'RFOUT': rf}
    for g in ('PB04', 'PB03', 'PB02', 'PB01', 'PA00', 'PA03', 'PA04', 'PA05', 'PA06', 'PA07', 'PA08', 'PD03', 'PD02', 'PD01', 'PD00', 'PC04', 'PC05', 'PC06', 'PC07'): n[g] = 'NC'
    part('U', 'MGM240P', n, val, mpn=mpn, mfr='Silicon Labs', alt='MGM240PB32VNA3 / MGM240PB32VNN3 pending certification check')
    c10u('+3V3'); c100n('+3V3')
    part('J', 'Connector_Generic:Conn_01x05', {1: '+3V3', 2: f'{tag}_SWDIO', 3: f'{tag}_SWCLK', 4: f'{tag}_RST_N', 5: G}, f'{tag} SWD',
         'Connector_PinHeader_1.27mm:PinHeader_1x05_P1.27mm_Vertical', '', '', 'SWD pads, not fitted', dnp=True)
mgm('ZB', 'MGM240PA32VNN3', 'ZB_RF_A', 'MGM240P Zigbee (RF pin)')
R('0', 'ZB_RF_A', 'ZB_RF_B', desc='0 ohm 0402, series element of antenna matching pi network')
C('DNP', 'ZB_RF_A', G, '0402', '50V', dnp=True, diel='C0G'); C('DNP', 'ZB_RF_B', G, '0402', '50V', dnp=True, diel='C0G')
part('J', 'Connector:Conn_Coaxial', {'In': 'ZB_RF_B', 'Ext': G}, 'U.FL Zigbee', 'Connector_Coaxial:U.FL_Hirose_U.FL-R-SMT-1_Vertical', 'U.FL-R-SMT-1(80)', 'Hirose', 'U.FL coaxial receptacle 50 ohm')
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      'TLV320AIC3100 is the I2S clock master, clocked by Y1 (12.288MHz = 256 x 48kHz); the CM5 I2S port is the clock consumer.\n'
      'One shared clock for capture and playback keeps the echo-cancellation reference sample-accurate. I2C address 0x18.\n'
      'MK1 is a bottom-port analog MEMS mic mounted on the bottom side over a 1.0mm acoustic hole. SW4 removes microphone\n'
      'power in hardware (privacy) and GPIO27 reports the state. Class-D output: 2.5W into 4 ohm from +5V.')
part('U', 'TLV320AIC3100',
     {'IOVSS': G, 'IOVDD': '+3V3', 'DVDD': '+1V8', 'DOUT': 'I2S_SDI', 'DIN': 'I2S_SDO', 'WCLK': 'I2S_WS', 'BCLK': 'I2S_BCLK', 'MCLK': 'AUD_MCLK', 'SDA': 'I2C1_SDA', 'SCL': 'I2C1_SCL',
      'VOL/MICDET': G, 'MICBIAS': 'NC', 'MIC1LP': 'MIC_IN_P', 'MIC1RP': 'NC', 'MIC1LM': 'MIC_IN_N', 'AVSS': G, 'AVDD': '+3V3A', 'DVSS': G, 'SPKM': 'SPK_M', 'SPKVSS': G,
      'SPKVDD': '+5V_SPK', 'SPKP': 'SPK_P', 'HPL': 'NC', 'HPVDD': '+3V3A', 'HPVSS': G, 'HPR': 'NC', '~{RESET}': 'AUD_RST_N', 'GPIO1': 'NC', 'EP': G},
     mpn='TLV320AIC3100IRHBR', mfr='Texas Instruments', alt='TLV320AIC3110IRHBR (stereo class-D, same driver)')
bead('+3V3', '+3V3A'); bead('+5V', '+5V_SPK', mpn='BLM21PG221SN1D', fp='Inductor_SMD:L_0805_2012Metric', val='220R@100MHz 2A')
for n in ('+3V3', '+1V8', '+3V3A', '+3V3A'): c100n(n); 
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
